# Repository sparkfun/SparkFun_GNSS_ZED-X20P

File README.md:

SparkFun Allband GNSS RTK Breakout - ZED-X20P (Qwiic)
========================================

[*SparkFun Allband GNSS RTK Breakout - ZED-X20P (Qwiic) (GPS-28871)*](https://www.sparkfun.com/sparkfun-allband-gnss-rtk-breakout-zed-x20p-qwiic.html)

The SparkFun All-band GNSS RTK Breakout - ZED-X20P (Qwiic) features the latest GNSS engine from u-blox; the X20, which is a successor to their popular F9 engine. This board's dimensions, pin layout, and connectors are very similar to the [SparkFun GPS-RTK-SMA Breakout - ZED-F9P (Qwiic)](https://www.sparkfun.com/sparkfun-gps-rtk-sma-breakout-zed-f9p-qwiic.html); and in most circumstances, can be used as a drop-in replacement. The board also accommodates users with a diverse choice of interfaces including USB, UART, SPI, and I<sup>2</sup>C.

The ZED-X20P module is an all-band, high precision GNSS receiver that concurrently processes signals from the GPS, Galileo, BeiDou, QZSS, and NavIC constellations across all GNSS frequency bands, including L-band. With positioning algorithms for Real-time Kinematics (RTK), PPP-RTK, and Precise Point Positioning* (PPP) technologies, the module supports standard RTCM corrections for Virtual Reference Stations (VRS) in a Network RTK setup or a local base station setup. Additionally, L-band correction services are natively supported without the need to integrate an external receiver, such as the NEO-D9S.

With its very high update rate, the ZED-X20P module is ideal for control applications, ensuring smooth and reliable operation. The module also protects system integrity with multi-layered defenses, including a Root of Trust, jamming and spoofing detection, cryptographic authentication of navigation messages through Galileo OSNMA, and more. This represents the highest level of integration in a single-chip receiver for the navigation and robotics markets; in unmanned autonomous vehicles (UAVs), guidance systems, and auto-steering applications.

The ZED-X20P module is supported by the u-blox u-center 2 GNSS software for real-time performance analysis, receiver configuration, and data logging. The AssistNow Online, Offline, and Autonomous A-GNSS services can also be used with the module for faster satellite acquisition. Users can also interface with the GNSS module using NMEA 4.11 and UBX binary protocols.

> [!NOTE]
> The USB interface does not fully comply with industry standards and is not suitable for production use. The USB 2.0 FS (full speed, 12 Mbit/s) interface can be used for host communication. Due to the hardware implementation, it may not be possible to certify the USB interface.
>
> `*`: Feature in development

Documentation
-------------

- **[Hookup Guide (mkdocs)](http://docs.sparkfun.com/SparkFun_GNSS_ZED-X20P/)** - A hookup guide for the SparkFun Allband GNSS RTK Breakout - ZED-X20P breakout board hosted by GitHub pages.<br>
   
- [SparkFun u-blox GNSS v3 Arduino Library](https://github.com/sparkfun/SparkFun_u-blox_GNSS_v3) - An Arduino library for the u-blox GNSS modules

Repository Contents
-------------------

- **[/docs](/docs/)** - Online documentation files
  - [/assets](/docs/assets/) - Assets files
    - [/3d_model](/docs/assets/3d_model/) - 3D models for the board
    - [/board_files](/docs/assets/board_files/) - Design files for the board
      - [KiCad Design Files](/docs/assets/board_files/kicad_files.zip) (.zip)
      - [Schematic](/docs/assets/board_files/schematic.pdf) (.pdf)
      - [Dimensions](/docs/assets/board_files/dimensions.pdf) (.pdf)
    - [/component_documentation](/docs/assets/component_documentation/) - Datasheets for hardware components
    - [/img/hookup_guide](/docs/assets/img/hookup_guide/) - Images for hookup guide documentation - Hookup guide images for the board
    - /Hardware - Hardware design files (.brd, .sch)
      - /Production - Production files

Product Variants
----------------

- [GPS-28871](https://www.sparkfun.com/sparkfun-allband-gnss-rtk-breakout-zed-x20p-qwiic.html) - Breakout Board
- Flex Modules
  - [GPS-29362](https://www.sparkfun.com/sparkpnt-gnss-flex-module-zed-x20p.html) - SparkPNT GNSS Flex Module
  - [GPS-28997](https://www.sparkfun.com/sparkpnt-gnss-flex-module-zed-x20p-im19-imu.html) - SparkPNT GNSS Flex Module w/ IMU
- pHAT Kits:
  - [GPS-29887](https://www.sparkfun.com/sparkfun-gnss-flex-phat-zed-x20p.html) - SparkFun GNSS Flex pHAT
  - [GPS-29888](https://www.sparkfun.com/sparkfun-gnss-flex-phat-zed-x20p-im19-imu.html) - SparkFun GNSS Flex pHAT w/ IMU

Version History
---------------

- [v10](https://github.com/sparkfun/SparkFun_GNSS_ZED-X20P/releases/tag/v10) - Initial Release

License Information
-------------------

This product is ***open source***!

Please review the [`LICENSE.md`](./LICENSE.md) file for license information.

If you have any questions or concerns about licensing, please contact technical support on our [SparkFun forums](https://forum.sparkfun.com/viewforum.php?f=152).

Distributed as-is; no warranty is given.

- Your friends at SparkFun.

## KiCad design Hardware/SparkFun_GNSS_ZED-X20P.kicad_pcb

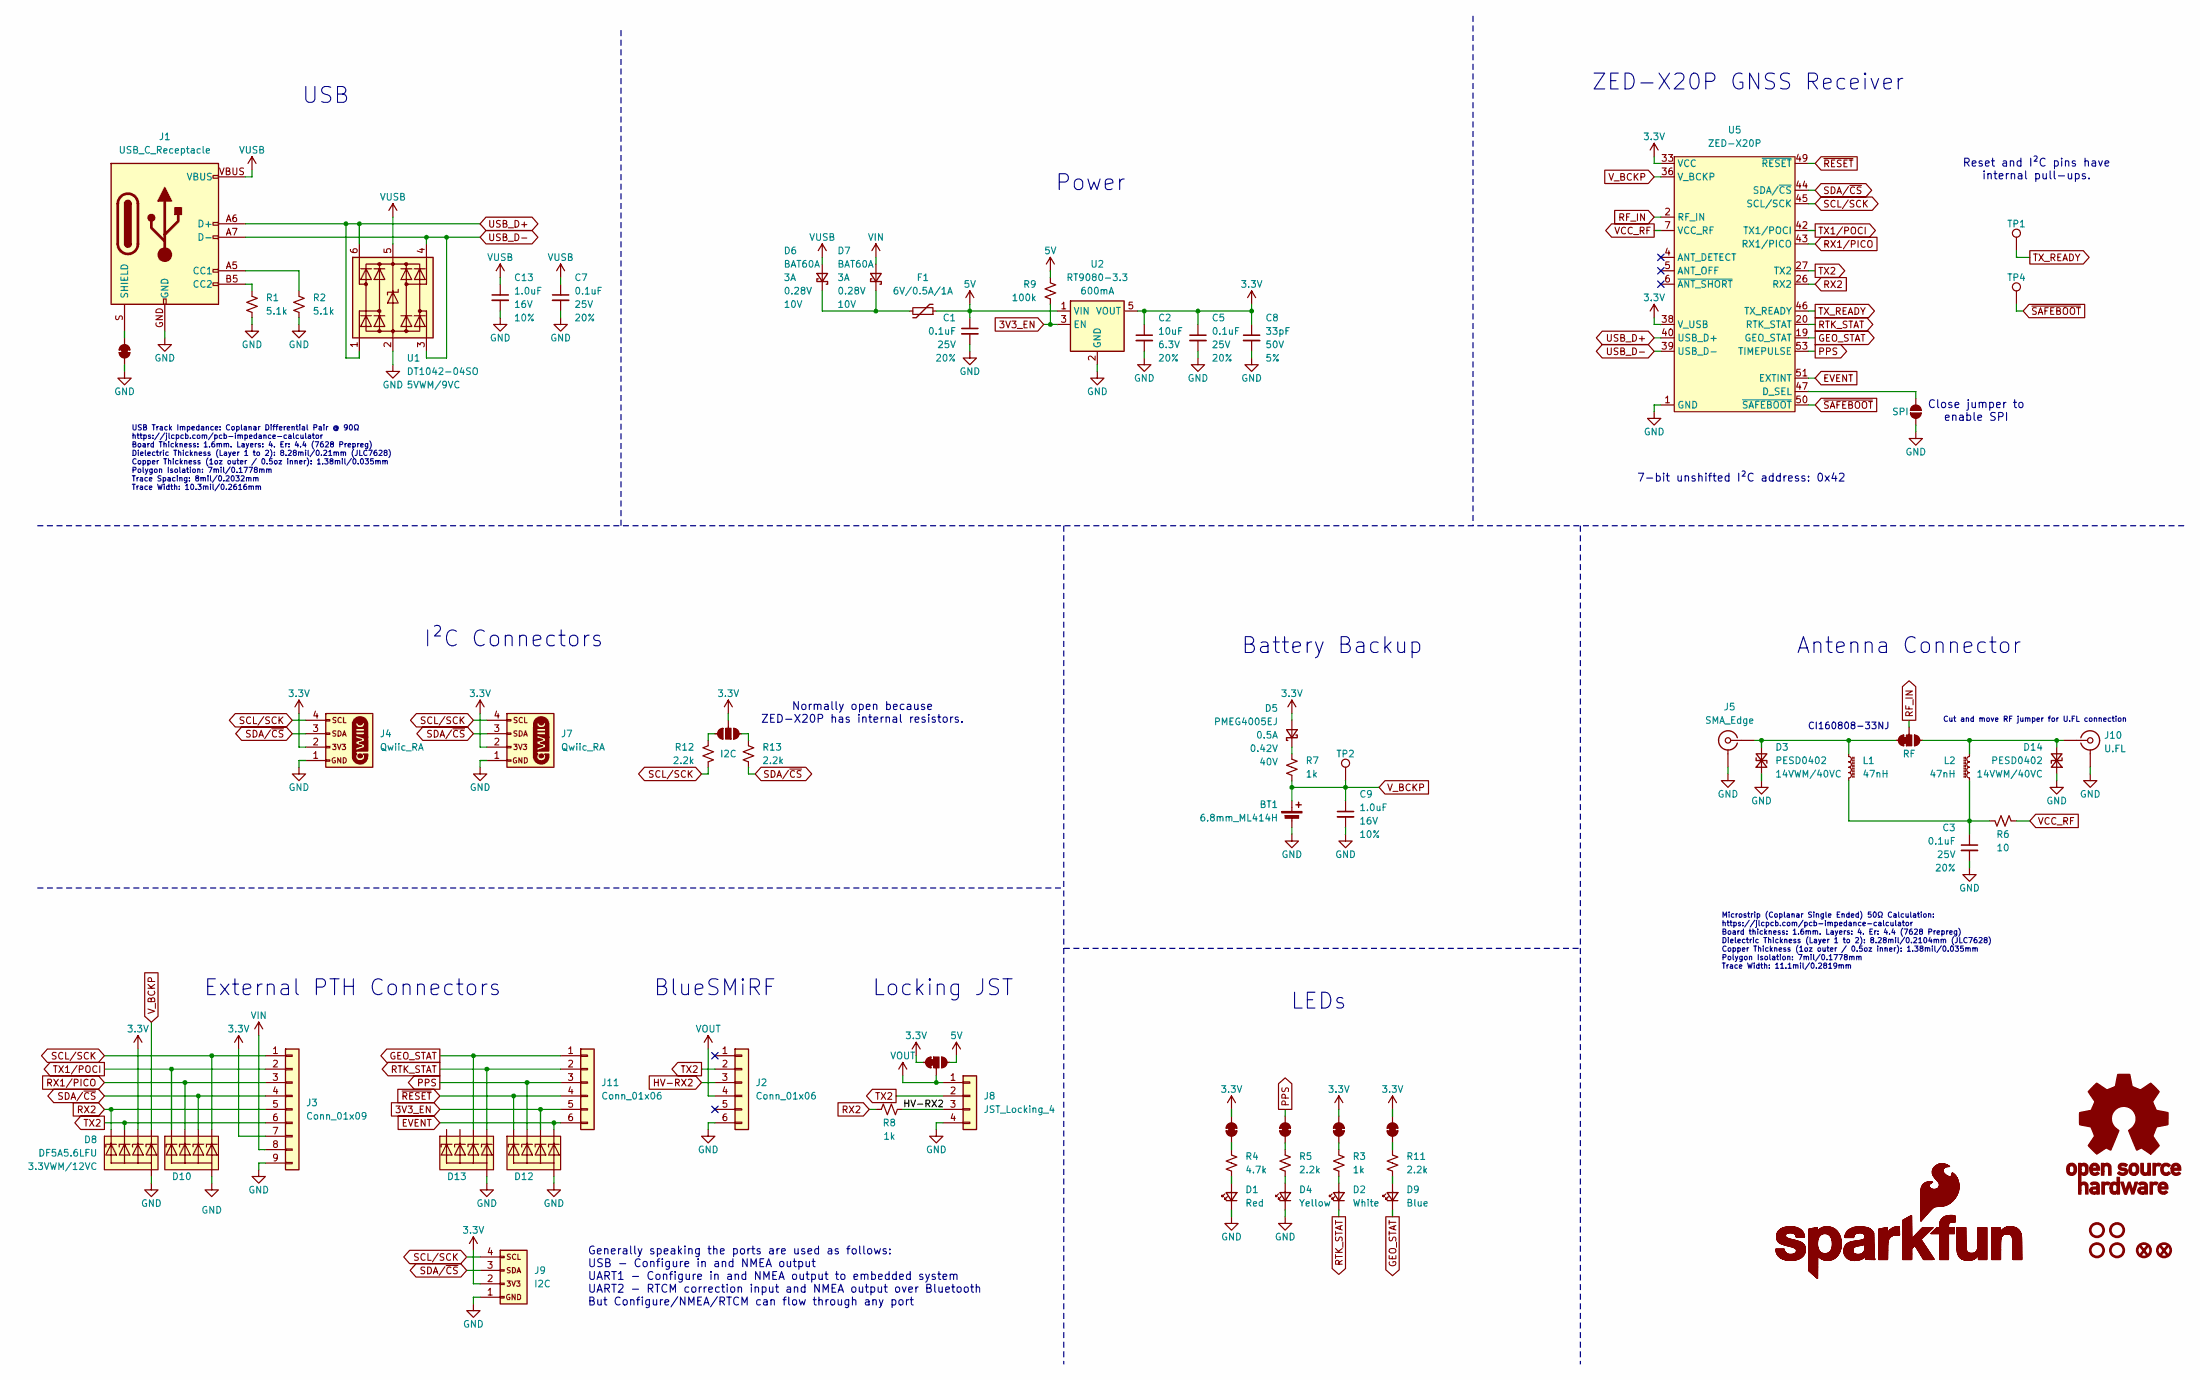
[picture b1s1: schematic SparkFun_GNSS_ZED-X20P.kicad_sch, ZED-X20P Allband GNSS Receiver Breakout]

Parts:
BT1: 6.8mm_ML414H; ML414H_IV01E
C1, C3, C5, C7: 0.1uF; C_0603_1608Metric; Voltage 25V; Tolerance 20%
C2: 10uF; C_0603_1608Metric; Voltage 6.3V; Tolerance 20%
C8: 33pF; C_0603_1608Metric; Voltage 50V; Tolerance 5%
C9, C13: 1.0uF; C_0603_1608Metric; Voltage 16V; Tolerance 10%
D1: Red; LED_0603_1608Metric_Red
D2: White; LED_0603_1608Metric_White
D3, D14: PESD0402; C_0402_1005Metric; Rating 14VWM/40VC
D4: Yellow; LED_0603_1608Metric_Yellow
D5: PMEG4005EJ; SOD-323
D6, D7: BAT60A; SOD-323
D8, D10, D12, D13: DF5A5.6LFU; SOT-353; Rating 3.3VWM/12VC
D9: Blue; LED_0603_1608Metric_Blue
F1: 6V/0.5A/1A; 0805
FID3, FID4: Fiducial_0.5mm; Fiducial_0.5mm_Mask1mm
G1: OSHW_Logo; Creative_Commons_License
G3: SparkFun_Logo
G5: SparkFun_Logo; SparkFun_Logo_8mm
J1: USB_C_Receptacle; USB-C_16
J2, J11: Conn_01x06; 1x06_P2.54mm
J3: Conn_01x09; 1x09_P2.54mm
J4, J7: Qwiic_RA; JST_1x04_P1.0mm_Horizontal_SMD
J5: SMA_Edge; SMA_Edge_8mm
J8: JST_Locking_4; JST_1x04_P1.25mm_Locking_Horizontal_SMD
J9: I2C; 1x04_P2.54mm
J10: U.FL
JP1: RF; Jumper_3_NC-1_Trace
JP2, JP3, JP5, JP7, JP8: Jumper_2_NC_Trace
JP4: Jumper_3_NC-1_Trace
JP9: I2C; Jumper_3_NO
JP10: SPI; Jumper_2_NO
L1, L2: 47nH; C_0603_1608Metric
R1, R2: 5.1k; R_0603_1608Metric
R3, R7, R8: 1k; R_0603_1608Metric
R4: 4.7k; R_0603_1608Metric
R5, R11, R12, R13: 2.2k; R_0603_1608Metric
R6: 10; R_0603_1608Metric
R9: 100k; R_0603_1608Metric
ST1, ST2, ST3, ST4: Standoff
TP1, TP2, TP4: 1.0mm; TestPoint-1.0mm
U1: DT1042-04SO; SOT23-6; Rating 5VWM/9VC
U2: RT9080-3.3; SOT23-5
U5: ZED-X20P; ZED-F9P_F9T_F9R_X20P

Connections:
3.3V: C2.1, C5.1, C8.1, D5.2 (A), D8.4 (K3), J3.7, J4.2, J7.2, J9.2, JP2.2 (B), JP4.1 (A), JP5.2 (B), JP8.2 (B), JP9.2 (B), U2.5 (VOUT), U5.33 (VCC), U5.34 (VCC), U5.38 (V_USB)
3V3_EN: D12.4 (K3), J11.5, R9.1, U2.3 (EN)
5V: C1.1, F1.1, JP4.3 (C), R9.2, U2.1 (VIN)
EVENT: D12.5 (K4), J11.6, U5.51 (EXTINT)
GEO_STAT: D9.1 (K), D13.4 (K3), J11.1, U5.19 (GEO_STAT)
GND: BT1.-, C1.2, C2.2, C3.2, C5.2, C7.2, C8.2, C9.2, C13.2, D1.1 (K), D3.1 (A1), D4.1 (K), D8.2 (A), D10.2 (A), D12.2 (A), D13.2 (A), D14.1 (A1), J1.GND, J2.6, J3.9, J4.1, J5.2 (Ext), J7.1, J8.4, J9.1, J10.2 (Ext), JP7.1 (A), JP10.1 (A), R1.1, R2.1, U1.2 (GND), U2.2 (GND), U5.1 (GND), U5.3 (GND), U5.12 (GND), U5.14 (GND), U5.32 (GND), U5.37 (GND), U5.41 (GND), U5.48 (GND), U5.55 (GND), U5.56 (GND), U5.57 (GND), U5.58 (GND), U5.59 (GND), U5.60 (GND), U5.61 (GND), U5.62 (GND), U5.63 (GND), U5.64 (GND), U5.65 (GND), U5.66 (GND), U5.67 (GND), U5.68 (GND), U5.69 (GND), U5.70 (GND), U5.71 (GND), U5.72 (GND), U5.73 (GND), U5.74 (GND), U5.75 (GND), U5.76 (GND), U5.77 (GND), U5.78 (GND), U5.79 (GND), U5.80 (GND), U5.81 (GND), U5.82 (GND), U5.83 (GND), U5.84 (GND), U5.85 (GND), U5.86 (GND), U5.87 (GND), U5.88 (GND), U5.89 (GND), U5.90 (GND), U5.91 (GND), U5.92 (GND), U5.93 (GND), U5.94 (GND), U5.95 (GND), U5.96 (GND), U5.97 (GND), U5.98 (GND), U5.99 (GND), U5.100 (GND), U5.101 (GND), U5.102 (GND)
HV-RX2: J2.3, J8.3, R8.1
unnamed: C3.1, L1.2, L2.2, R6.2
unnamed: D1.2 (A), R4.1
unnamed: D2.2 (A), R3.1
unnamed: D3.2 (A2), J5.1 (In), JP1.1 (A), L1.1
unnamed: D4.2 (A), R5.1
unnamed: D5.1 (K), R7.2
unnamed: D6.1 (K), D7.1 (K), F1.2
unnamed: D9.2 (A), R11.1
unnamed: D14.2 (A2), J10.1 (In), JP1.3 (C), L2.1
unnamed: J1.A5 (CC1), R2.2
unnamed: J1.B5 (CC2), R1.2
unnamed: J1.S (SHIELD), JP7.2 (B)
unnamed: JP2.1 (A), R4.2
unnamed: JP3.1 (A), R5.2
unnamed: JP5.1 (A), R3.2
unnamed: JP8.1 (A), R11.2
unnamed: JP9.1 (A), R13.1
unnamed: JP9.3 (C), R12.1
unnamed: JP10.2 (B), U5.47 (D_SEL)
PPS: D12.3 (K2), J11.3, JP3.2 (B), U5.53 (TIMEPULSE)
RF_IN: JP1.2 (B), U5.2 (RF_IN)
RTK_STAT: D2.1 (K), D13.5 (K4), J11.2, U5.20 (RTK_STAT)
RX1/PICO: D10.3 (K2), J3.3, U5.43 (RX1/PICO)
RX2: D8.1 (K1), J3.5, R8.2, U5.26 (RX2)
SCL/SCK: D10.5 (K4), J3.1, J4.4, J7.4, J9.4, R12.2, U5.45 (SCL/SCK)
SDA/~CS: D10.4 (K3), J3.4, J4.3, J7.3, J9.3, R13.2, U5.44 (SDA/~CS)
TX1/POCI: D10.1 (K1), J3.2, U5.42 (TX1/POCI)
TX2: D8.3 (K2), J2.2, J3.6, J8.2, U5.27 (TX2)
TX_READY: TP1.1, U5.46 (TX_READY)
USB_D+: J1.A6 (D+), J1.B6 (D+), U1.1 (I/O1), U1.6 (I/O4), U5.40 (USB_D+)
USB_D-: J1.A7 (D-), J1.B7 (D-), U1.3 (I/O2), U1.4 (I/O3), U5.39 (USB_D-)
VCC_RF: R6.1, U5.7 (VCC_RF)
VIN: D7.2 (A), J3.8
VOUT: J2.4, J8.1, JP4.2 (B)
VUSB: C7.1, C13.1, D6.2 (A), J1.VBUS, U1.5 (VCC)
V_BCKP: BT1.+, C9.1, D8.5 (K4), R7.1, TP2.1, U5.36 (V_BCKP)
~RESET: D12.1 (K1), J11.4, U5.49 (~RESET)
~SAFEBOOT: TP4.1, U5.50 (~SAFEBOOT)

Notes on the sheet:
7-bit unshifted I²C address: 0x42
CI160808-33NJ
I²C Connectors
Microstrip (Coplanar Single Ended) 50Ω Calculation: https://jlcpcb.com/pcb-impedance-calculator Board thickness: 1.6mm. Layers: 4. Er: 4.4 (7628 Prepreg) Dielectric Thickness (Layer 1 to 2): 8.28mil/0.2104mm (JLC7628) Copper Thickness (1oz outer / 0.5oz inner): 1.38mil/0.035mm Polygon Isolation: 7m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
Generally speaking the ports are used as follows: USB - Configure in and NMEA output UART1 - Configure in and NMEA output to embedded system UART2 - RTCM correction input and NMEA output over Bluetooth But Configure/NMEA/RTCM can flow through any port
USB Track Impedance: Coplanar Differential Pair @ 90Ω https://jlcpcb.com/pcb-impedance-calculator Board Thickness: 1.6mm. Layers: 4. Er: 4.4 (7628 Prepreg) Dielectric Thickness (Layer 1 to 2): 8.28mil/0.21mm (JLC7628) Copper Thickness (1oz outer / 0.5oz inner): 1.38mil/0.035mm Polygon Isolation: 7m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
Cut and move RF jumper for U.FL connection
BlueSMiRF
Reset and I²C pins have internal pull-ups.
Locking JST
Power
Antenna Connector
LEDs
ZED-X20P GNSS Receiver
Close jumper to enable SPI
USB
Battery Backup
External PTH Connectors
Normally open because ZED-X20P has internal resistors.

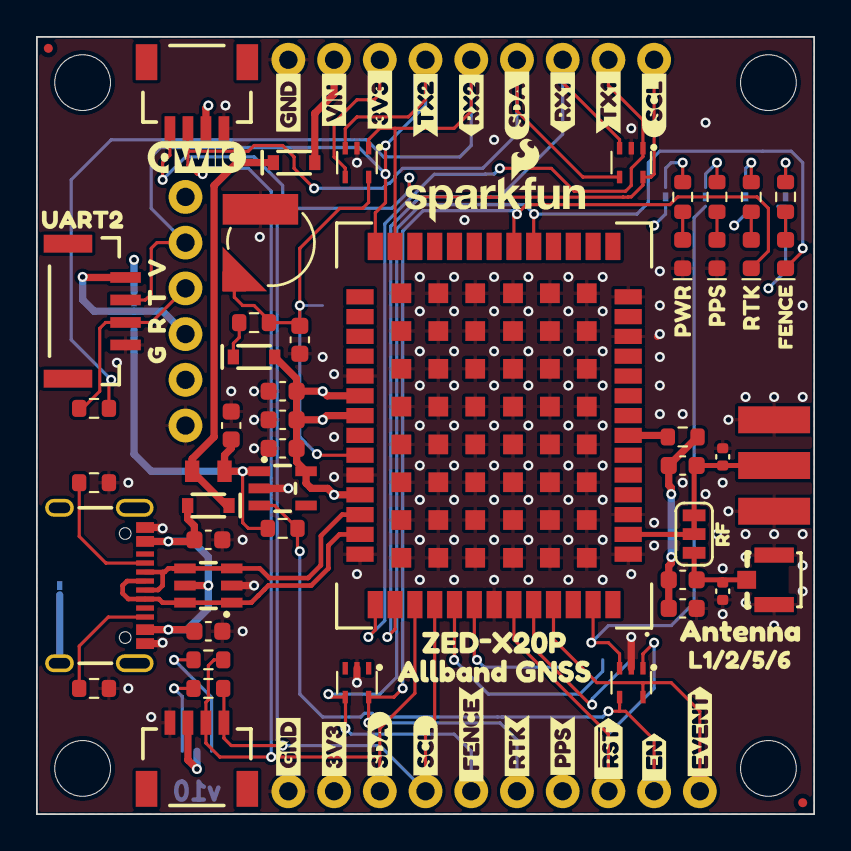
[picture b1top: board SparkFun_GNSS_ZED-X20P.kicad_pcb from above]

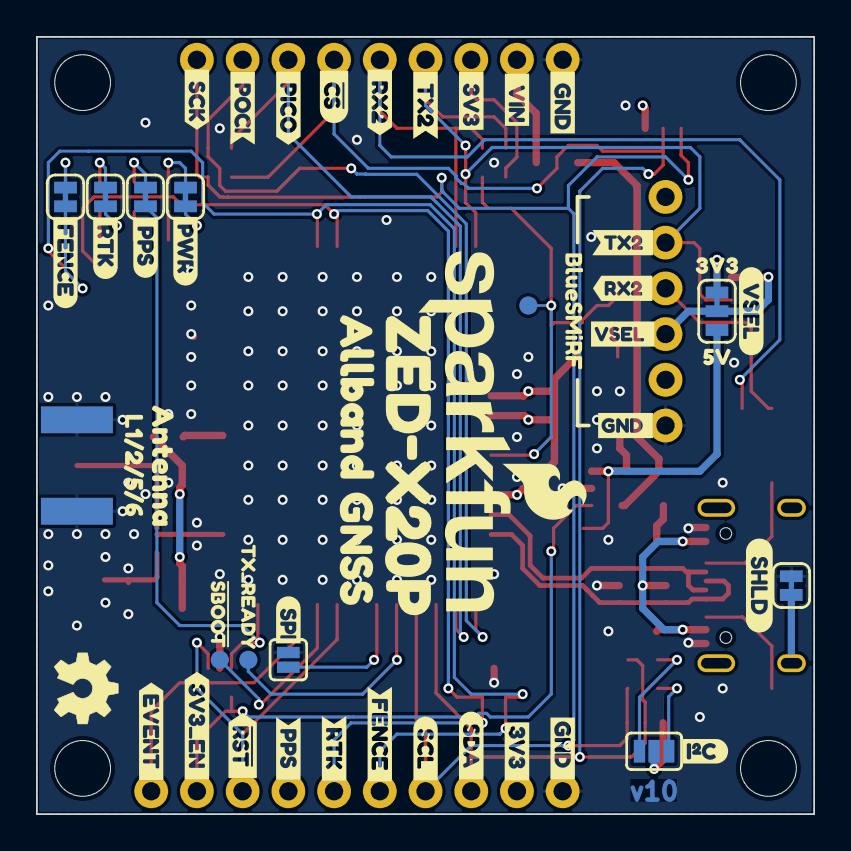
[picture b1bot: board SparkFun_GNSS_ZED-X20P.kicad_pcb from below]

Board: 4 copper layers, 43.2 x 43.2 mm, 140 parts (52 on the bottom side), 45 nets.

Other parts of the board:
Ref**: Val**; OSHW_Logo_4mm
kibuzzard-64C2E6A3: G***; kibuzzard-64C2E6A3
kibuzzard-64C2E6BD: G***; kibuzzard-64C2E6BD
kibuzzard-64C2E6D6: G***; kibuzzard-64C2E6D6
kibuzzard-64C3DF93: G***; kibuzzard-64C3DF93
kibuzzard-66CAA7B2: G***; kibuzzard-66CAA7B2
kibuzzard-66CAA41A: G***; kibuzzard-66CAA41A
kibuzzard-66CAA426: G***; kibuzzard-66CAA426
kibuzzard-66CAA432: G***; kibuzzard-66CAA432
kibuzzard-66CAA594: G***; kibuzzard-66CAA594
kibuzzard-66CB82FB: G***; kibuzzard-66CB82FB
kibuzzard-66CB829C: G***; kibuzzard-66CB829C
kibuzzard-66CB830B: G***; kibuzzard-66CB830B
kibuzzard-67EC5C53: G***; kibuzzard-67EC5C53
kibuzzard-67EC52D7: G***; kibuzzard-67EC52D7
kibuzzard-67EC52E7: G***; kibuzzard-67EC52E7
kibuzzard-67EC55E2: G***; kibuzzard-67EC55E2
kibuzzard-67EC56CE, kibuzzard-67EC56CE#2: G***; kibuzzard-67EC56CE
kibuzzard-67EC56E0, kibuzzard-67EC56E0#2: G***; kibuzzard-67EC56E0
kibuzzard-67EC56FC: G***; kibuzzard-67EC56FC
kibuzzard-67EC530B: G***; kibuzzard-67EC530B
kibuzzard-67EC532A: G***; kibuzzard-67EC532A
kibuzzard-67EC572D: G***; kibuzzard-67EC572D
kibuzzard-67EC5004: G***; kibuzzard-67EC5004
kibuzzard-67EC5083: G***; kibuzzard-67EC5083
kibuzzard-67EC5549: G***; kibuzzard-67EC5549
kibuzzard-67EC5701: G***; kibuzzard-67EC5701
kibuzzard-67EC5939: G***; kibuzzard-67EC5939
kibuzzard-67ED9A4D: G***; kibuzzard-67ED9A4D
kibuzzard-67ED9A5A: G***; kibuzzard-67ED9A5A
kibuzzard-67ED9A5D: G***; kibuzzard-67ED9A5D
kibuzzard-67ED9A28: G***; kibuzzard-67ED9A28
kibuzzard-67ED9A70: G***; kibuzzard-67ED9A70
kibuzzard-67ED9C3D: G***; kibuzzard-67ED9C3D
kibuzzard-67ED9D32: G***; kibuzzard-67ED9D32
kibuzzard-67ED9ED8: G***; kibuzzard-67ED9ED8
kibuzzard-67ED93D1: G***; kibuzzard-67ED93D1
kibuzzard-680A971A: G***; kibuzzard-680A971A
kibuzzard-680A972D: G***; kibuzzard-680A972D
kibuzzard-680A9713: G***; kibuzzard-680A9713
kibuzzard-680A9725: G***; kibuzzard-680A9725
kibuzzard-6501FDDA: G***; kibuzzard-6501FDDA
kibuzzard-6797CE3B: G***; kibuzzard-6797CE3B
kibuzzard-6797CE4B: G***; kibuzzard-6797CE4B
kibuzzard-6797CE48: G***; kibuzzard-6797CE48
kibuzzard-6797CF40: G***; kibuzzard-6797CF40
kibuzzard-6797CFD5: G***; kibuzzard-6797CFD5
kibuzzard-6797CFD9: G***; kibuzzard-6797CFD9
kibuzzard-6797CFEB: G***; kibuzzard-6797CFEB
kibuzzard-6797D0AD: G***; kibuzzard-6797D0AD
kibuzzard-6797D0B5: G***; kibuzzard-6797D0B5
kibuzzard-6797D0B9: G***; kibuzzard-6797D0B9
kibuzzard-6797D0BE: G***; kibuzzard-6797D0BE
kibuzzard-6797D1E0: G***; kibuzzard-6797D1E0
kibuzzard-6797D04A: G***; kibuzzard-6797D04A
kibuzzard-6797D04F: G***; kibuzzard-6797D04F
kibuzzard-6797D06C: G***; kibuzzard-6797D06C
kibuzzard-6797D07B: G***; kibuzzard-6797D07B
kibuzzard-6797D08B: G***; kibuzzard-6797D08B
kibuzzard-6797D08F: G***; kibuzzard-6797D08F
kibuzzard-6797D21D: G***; kibuzzard-6797D21D
kibuzzard-6797D058: G***; kibuzzard-6797D058
kibuzzard-6797D071: G***; kibuzzard-6797D071
kibuzzard-6797D081: G***; kibuzzard-6797D081
kibuzzard-6797D086: G***; kibuzzard-6797D086
kibuzzard-6797D093: G***; kibuzzard-6797D093
kibuzzard-6797D096: G***; kibuzzard-6797D096
kibuzzard-6797D214: G***; kibuzzard-6797D214
kibuzzard-6797D229: G***; kibuzzard-6797D229

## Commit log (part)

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2025-04-02 Post airwire review
2025-04-03 Update to v9.
2025-04-23 Add CH342
2025-04-24 Add panel
2025-05-21 Add HPG 2.00 firmware
2025-09-10 Update .gitignore
    Remove leftover merge conflict markers
    Consolidate duplicate entries
2025-09-10 Deployed 3a21fed with MkDocs version: 1.6.1
2025-09-10 Deployed 0b0db96 with MkDocs version: 1.6.1
2025-09-10 Deployed 71e4e8b with MkDocs version: 1.6.1
2025-09-12 Initial Docs Commit
2025-09-17 Deployed bad17bb with MkDocs version: 1.6.1
2025-09-17 Deployed f283d1e with MkDocs version: 1.6.1
2025-10-06 Deployed 1033ed5 with MkDocs version: 1.6.1
2025-10-14 Move HPG200 firmware files into subdirectory
    Moved HPG200-related firmware and documentation files into a dedicated 'HPG200' subdirectory
2025-10-14 HPG 2.02 firmware update
    Added HPG 2.02 firmware and documentation files
    Updated hookup guide
    - Updated component documentation files for new firmware
    - Revised hardware specs, configuration, and protocol details for new firmware
2025-10-14 Deployed 74be415 with MkDocs version: 1.6.1
2025-10-14 Update workflow
    Use requirements.txt to install dependencies
    Remove submodule implementation
2025-10-14 Remove configuration interface
    Accidentally committed information
2025-10-14 Update resources.md
    Remove comment block
2025-10-30 Update forum link
2025-11-13 Update to new symbol/fp locations

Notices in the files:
parts and their libraries:
https://creativecommons.org/licenses/by-sa/4.0
Released under the Creative Commons Attribution Share-Alike 4.0 License
